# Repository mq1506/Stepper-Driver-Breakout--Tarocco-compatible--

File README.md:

# Tarocco-compatible-Stepper-Driver-Breakout
(Untested) Breakout for the stepper drive interface (polulu carrier board) used in almost every 3d printer with replaceable Drivers.
Designed to be directly compatible with the control port on the Tarocco Servo Drive https://www.crowdsupply.com/citrus-cnc/tarocco but it can also be used for hooking up other external drivers.

The 3 pins at the top are to allow the use of a jumper to tie the error and reset together to stop motion when a fault occurs or to tie the enable pin to the reset and allow you to disable the Tarocco without removing power (useful for removing prints from a bed on a 3d printer). Currently this isn't supported by the Tarocco firmware but it would be an easy change. These pins are also useful for tying multiple driver error and reset lines together so they act as one.

Posting under a Creative Commons Attribution, Share-Alike (BY-SA) Liscence

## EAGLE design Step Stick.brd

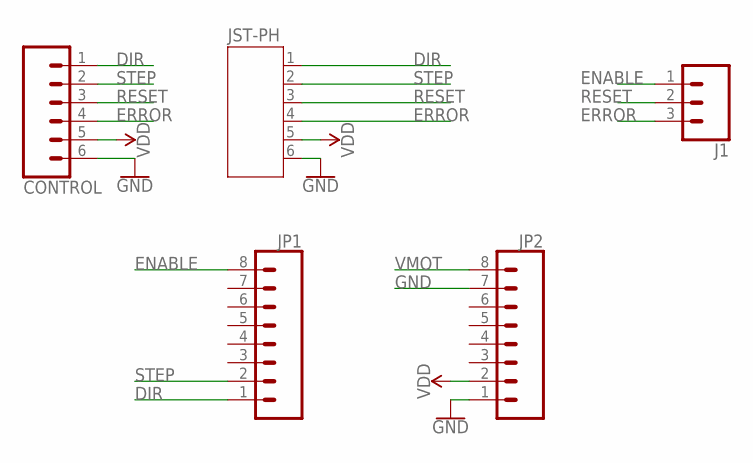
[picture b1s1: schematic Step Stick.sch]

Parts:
CONTROL: CONN_06NO_SILK_FEMALE_PTH; 1X06_NO_SILK
J1: CONN_031X03_NO_SILK; 1X03_NO_SILK
JP1, JP2: CONN_08NO_SILK_FEMALE_PTH; 1X08_NO_SILK
JST-PH: JST-PH6

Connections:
DIR: CONTROL.1, JP1.1, JST-PH.1
ENABLE: J1.1, JP1.8
ERROR: CONTROL.4, J1.3, JST-PH.4
GND: CONTROL.6, JP2.1, JP2.7, JST-PH.6
RESET: CONTROL.3, J1.2, JST-PH.3
STEP: CONTROL.2, JP1.2, JST-PH.2
VDD: CONTROL.5, JP2.2, JST-PH.5
VMOT: JP2.8

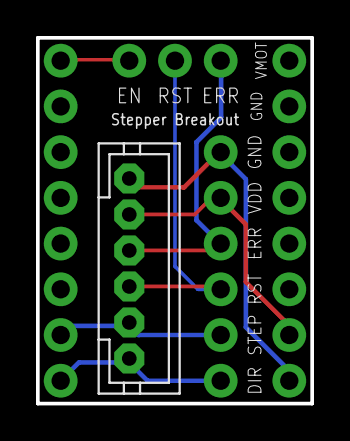
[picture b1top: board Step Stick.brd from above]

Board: 2 copper layers, 15.2 x 20.3 mm, 5 parts (0 on the bottom side), 7 nets.

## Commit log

2017-01-22 :neckbeard: Added .gitattributes & .gitignore files
2017-01-22 updated .gitignore
2017-01-22 Remove ignored files
2017-01-22 Added images
2017-01-22 Moved labels to make them more visible

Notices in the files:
parts and their libraries:
SparkFun-Connectors: Licensing: CC v3.0 Share-Alike You are welcome to use this library for commercial purposes.
SparkFun-PowerSymbols: Licensing: Creative Commons ShareAlike 4.0 International - https://creativecommons.org/licenses/by-sa/4.0
